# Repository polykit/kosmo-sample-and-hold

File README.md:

# Kosmo Sample&Hold / Noise module

This repository contains KiCad schematics and PCB layout for a sample and hold / white noise module in Kosmo synthesizer format. Gerber files can be found [here](plots).

## Schematics

## BOM

|Reference             |Quantity|Value               |
|----------------------|--------|--------------------|
|C1                    |1       |1n                  |
|C2                    |1       |47u                 |
|C3                    |1       |1u                  |
|C4                    |1       |100n*               |
|C6 C7                 |2       |10u                 |
|C8                    |1       |100n                |
|D1 D2                 |2       |1N4148              |
|IN1 OUT1 NOISE1 TRIG1 |4       |6.35mm audio jacks  |
|POWER1                |1       |10 pin IDC connector|
|Q1                    |1       |J113                |
|Q2                    |1       |BC547               |
|R1 R11 R13 R14        |4       |1k                  |
|R15 R16               |2       |10                  |
|R3 R7                 |2       |100                 |
|R2 R4 R5 R10 R12      |5       |100k                |
|R6                    |1       |10k                 |
|R8 R9                 |2       |1M                  |
|U1                    |1       |TL074               |

\* use film capacitor for better results

## References

https://www.schmitzbits.de/sah.html

https://yusynth.net/Modular/EN/NOISE/index.html

https://i.imgur.com/u3f4tQ6.jpg

https://www.lookmumnocomputer.com/modular

https://github.com/telec16/kicad

https://github.com/holmesrichards/Kosmo_panel

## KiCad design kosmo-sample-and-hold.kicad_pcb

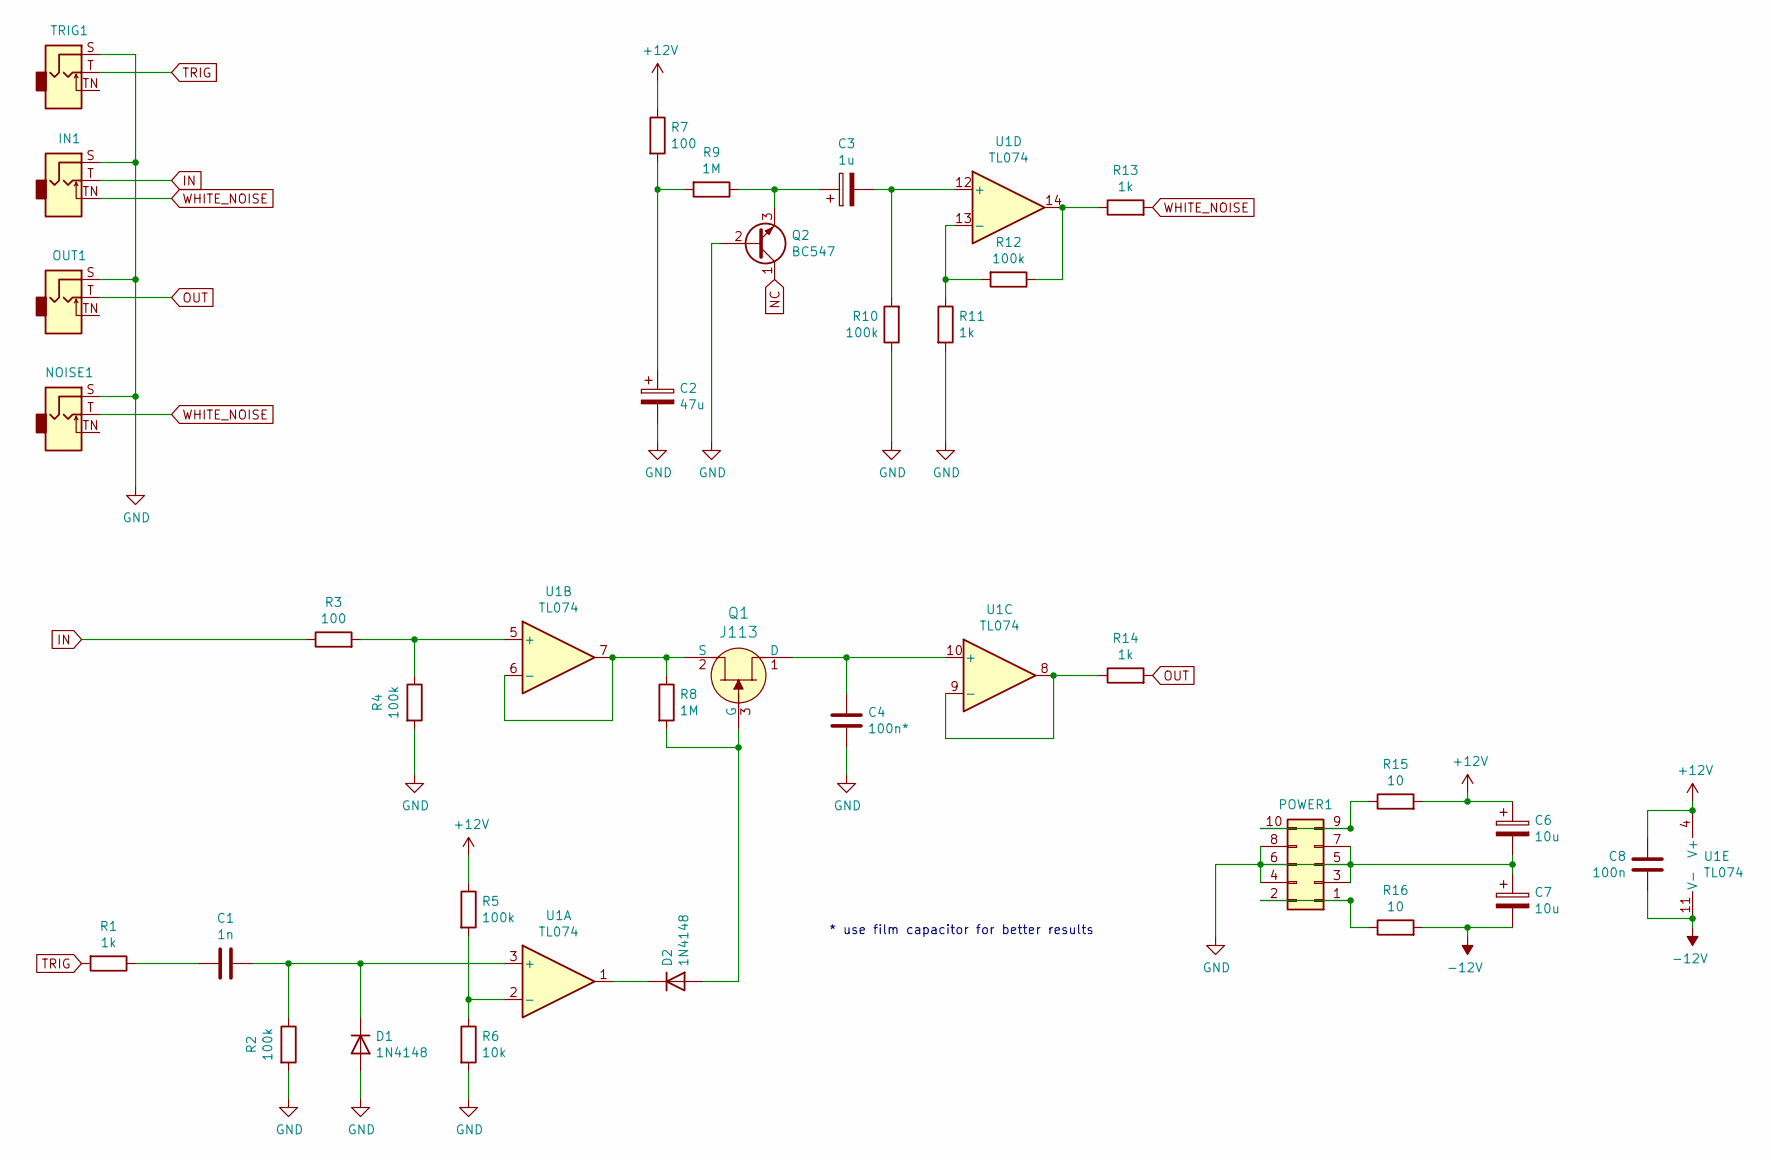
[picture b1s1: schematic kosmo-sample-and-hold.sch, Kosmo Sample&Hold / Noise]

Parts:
C1: 1n; C_Disc_D5.0mm_W2.5mm_P5.00mm
C2: 47u; CP_Radial_D6.3mm_P2.50mm
C3: 1u; CP_Radial_D5.0mm_P2.50mm
C4: 100n*; C_Disc_D5.0mm_W2.5mm_P5.00mm
C6, C7: 10u; CP_Radial_D5.0mm_P2.50mm
C8: 100n; C_Disc_D5.0mm_W2.5mm_P5.00mm
D1, D2: 1N4148; D_DO-35_SOD27_P7.62mm_Horizontal
IN1: AudioJack2_SwitchT; Jack_Hole_Square
NOISE1: AudioJack2_SwitchT; Jack_Hole_Square
OUT1: AudioJack2_SwitchT; Jack_Hole_Square
POWER1: Conn_02x05_Odd_Even; IDC-Header_2x05_P2.54mm_Vertical
Q1: J113; TO-92_Inline_Wide; MPN J113; Digi-Key_PN J113FS-ND
Q2: BC547; TO-92_Inline_Wide
R1, R11, R13, R14: 1k; R_Axial_DIN0207_L6.3mm_D2.5mm_P10.16mm_Horizontal
R2, R4, R5, R10, R12: 100k; R_Axial_DIN0207_L6.3mm_D2.5mm_P10.16mm_Horizontal
R3, R7: 100; R_Axial_DIN0207_L6.3mm_D2.5mm_P10.16mm_Horizontal
R6: 10k; R_Axial_DIN0207_L6.3mm_D2.5mm_P10.16mm_Horizontal
R8, R9: 1M; R_Axial_DIN0207_L6.3mm_D2.5mm_P10.16mm_Horizontal
R15, R16: 10; R_Axial_DIN0207_L6.3mm_D2.5mm_P10.16mm_Horizontal
TRIG1: AudioJack2_SwitchT; Jack_Hole_Square
U1: TL074; DIP-14_W7.62mm_Socket_LongPads

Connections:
+12V: C6.1, C8.1, R5.1, R7.1, R15.2, U1.4 (V+)
-12V: C7.2, C8.2, R16.2, U1.11 (V-)
GND: C2.2, C4.2, C6.2, C7.1, D1.2 (A), IN1.S, NOISE1.S, OUT1.S, POWER1.3, POWER1.4, POWER1.5, POWER1.6, POWER1.7, POWER1.8, Q2.2 (B), R2.2, R4.2, R6.2, R10.1, R11.2, TRIG1.S
IN: IN1.T, R3.1
NC: Q2.1 (C)
unnamed: C1.1, D1.1 (K), R2.1, U1.3 (+)
unnamed: C1.2, R1.1
unnamed: C2.1, R7.2, R9.2
unnamed: C3.1, Q2.3 (E), R9.1
unnamed: C3.2, R10.2, U1.12 (+)
unnamed: C4.1, Q1.1 (D), U1.10 (+)
unnamed: D2.1 (K), U1.1
unnamed: D2.2 (A), Q1.3 (G), R8.2
unnamed: POWER1.1, POWER1.2, R16.1
unnamed: POWER1.9, POWER1.10, R15.1
unnamed: Q1.2 (S), R8.1, U1.6 (-), U1.7
unnamed: R3.2, R4.1, U1.5 (+)
unnamed: R5.2, R6.1, U1.2 (-)
unnamed: R11.1, R12.2, U1.13 (-)
unnamed: R12.1, R13.1, U1.14
unnamed: R14.1, U1.8, U1.9 (-)
OUT: OUT1.T, R14.2
TRIG: R1.2, TRIG1.T
WHITE_NOISE: IN1.TN, NOISE1.T, R13.2

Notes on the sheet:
* use film capacitor for better results

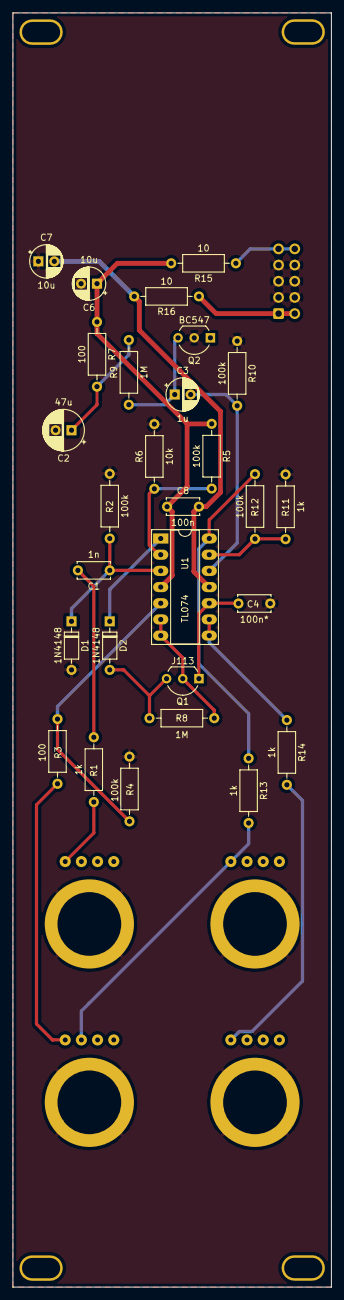
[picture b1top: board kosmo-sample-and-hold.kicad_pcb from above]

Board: 2 copper layers, 50.0 x 200.0 mm, 33 parts (1 on the bottom side), 23 nets.

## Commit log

2021-03-12 Initial import
2021-03-12 Added gerber files
2021-10-08 Add image for modulargrid
2021-10-08 Add small multigrid image
2021-10-08 Changes readme
2021-10-26 Use BC547 for noise
